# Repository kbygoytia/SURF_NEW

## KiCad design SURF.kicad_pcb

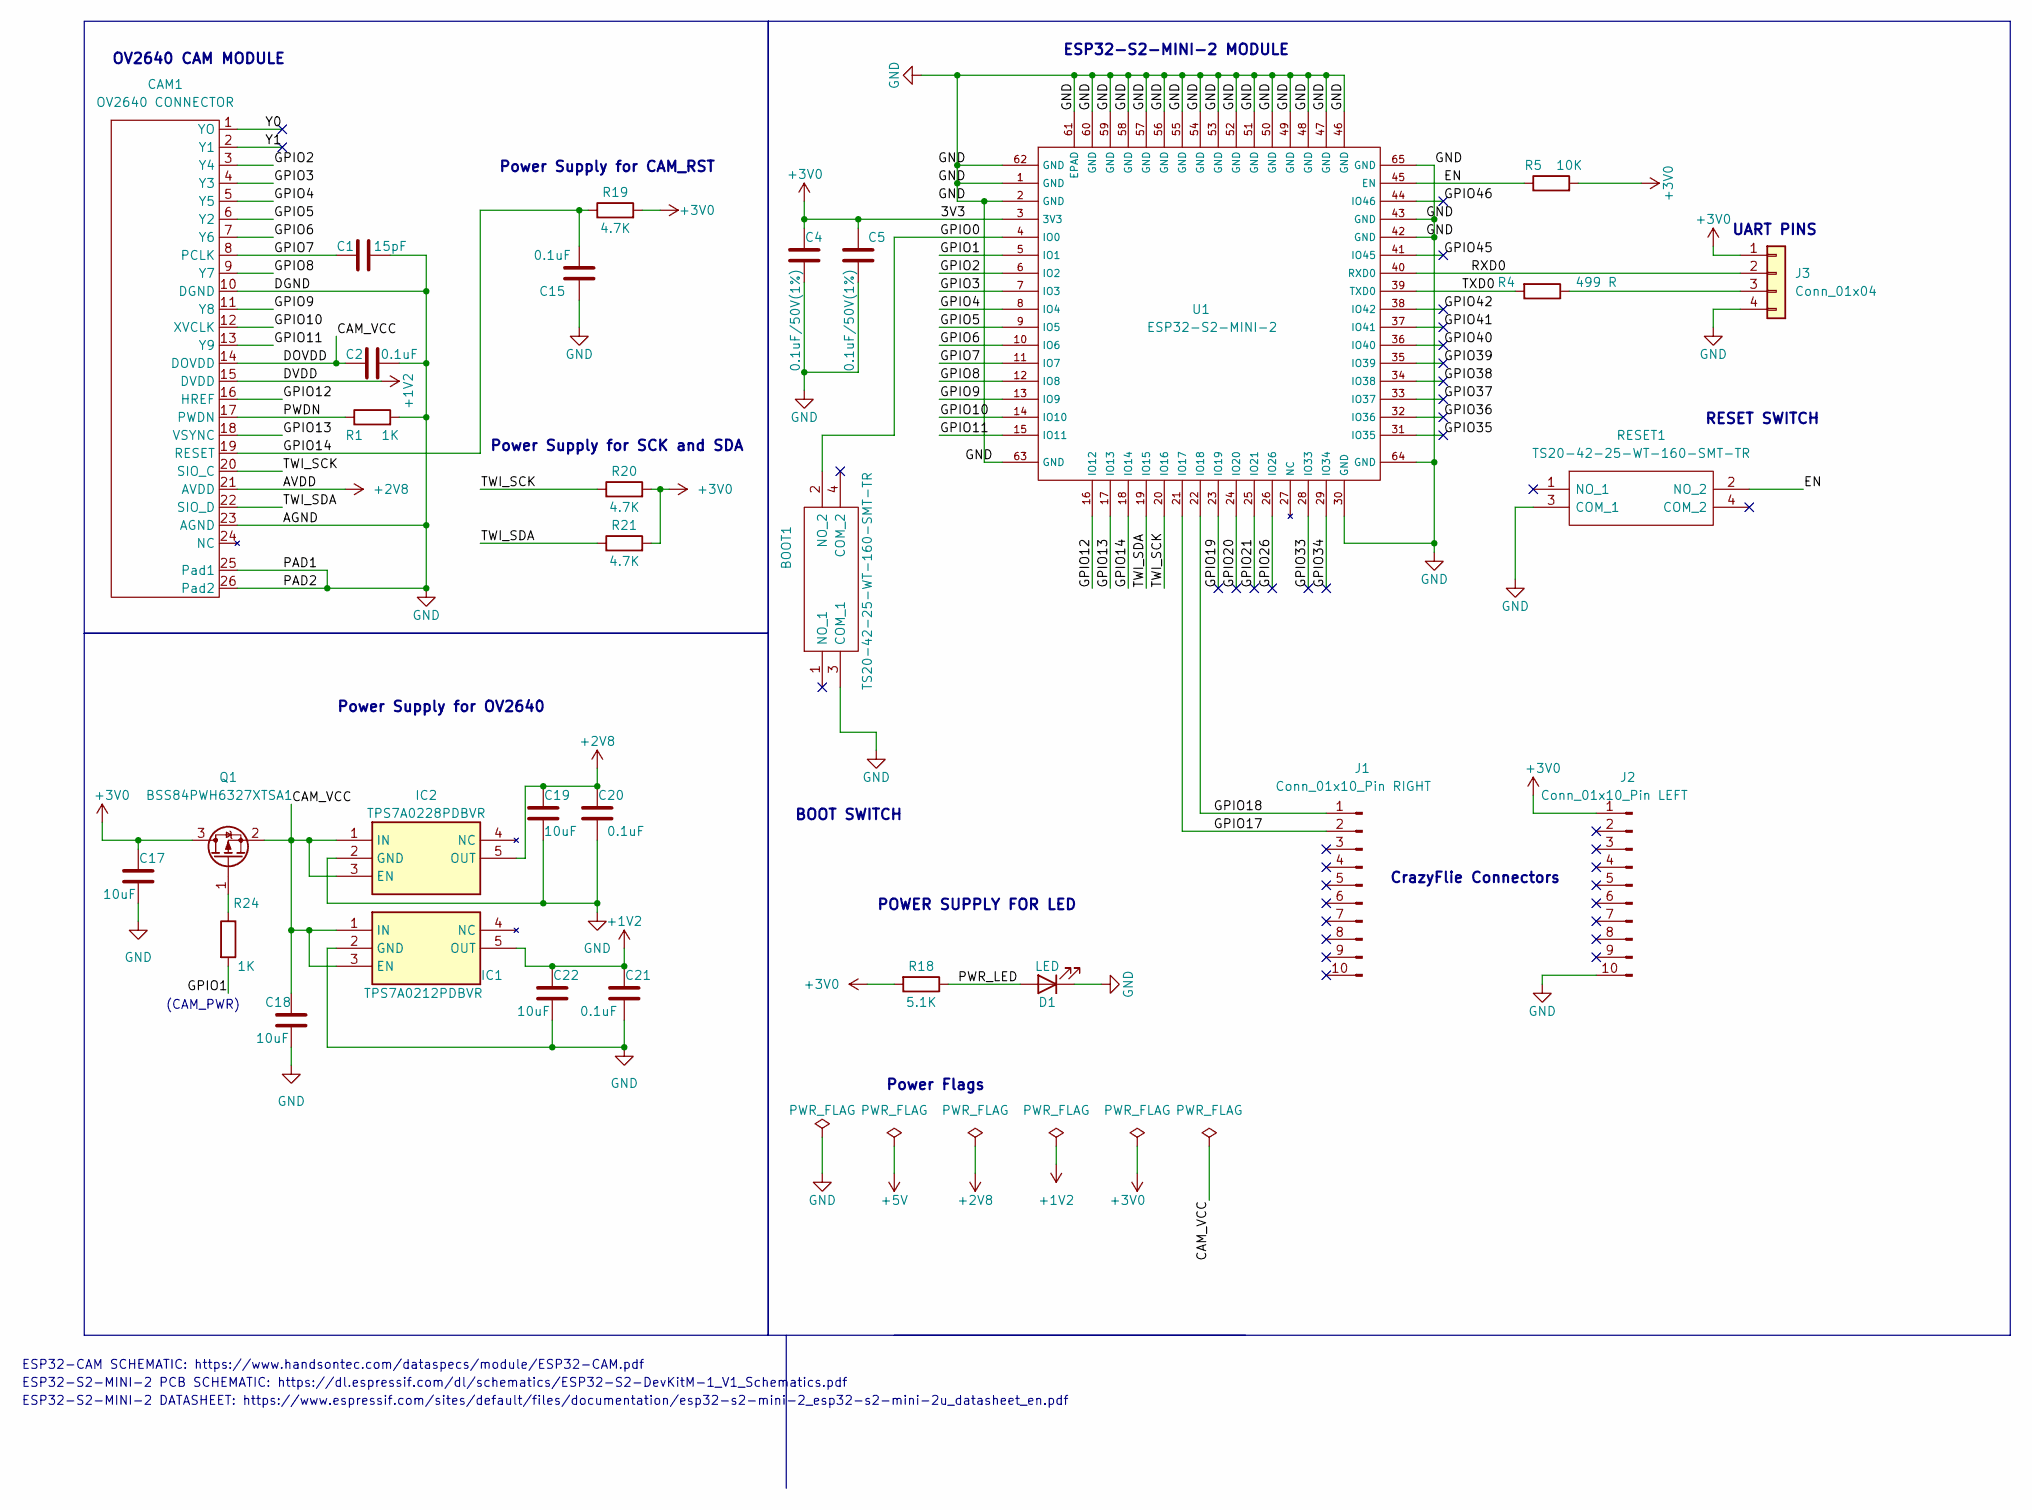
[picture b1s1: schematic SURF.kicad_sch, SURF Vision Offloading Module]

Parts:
BOOT1: TS20-42-25-WT-160-SMT-TR; TS204225WT160SMTTR; Mouser Part Number 179-TS204225WT160SMT
C1: 15pF; CAPC1608X87N
C2, C15, C20, C21: 0.1uF; CAPC1608X90N
C4, C5: 0.1uF/50V(1%); CAPC3216X170N
C17, C18, C19, C22: 10uF; CAPC2012X145N
CAM1: OV2640 CONNECTOR; ov2640-fcp_1
D1: LED; LED_0603_1608Metric
IC1: TPS7A0212PDBVR; SOT95P280X145-5N; Mouser Part Number 595-TPS7A0212PDBVR
IC2: TPS7A0228PDBVR; SOT95P280X145-5N; Mouser Part Number 595-TPS7A0228PDBVR
J1: Conn_01x10_Pin RIGHT; CONN_PINHEADERS_01X10_CRAZYFLIE
J2: Conn_01x10_Pin LEFT; CONN_PINHEADERS_01X10_CRAZYFLIE
J3: Conn_01x04; PinHeader_1x04_P2.54mm_Vertical
Q1: BSS84PWH6327XTSA1; SOT-523
R1, R24: 1K; R_0402_1005Metric
R4: 499 R; R_0402_1005Metric
R5: 10K; R_0402_1005Metric
R18: 5.1K; R_0402_1005Metric
R19, R20, R21: 4.7K; R_0402_1005Metric
RESET1: TS20-42-25-WT-160-SMT-TR; TS204225WT160SMTTR; Mouser Part Number 179-TS204225WT160SMT
U1: ESP32-S2-MINI-2

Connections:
+1V2: C21.1, C22.1, CAM1.15 (DVDD), IC1.5 (OUT)
+2V8: C19.1, C20.1, CAM1.21 (AVDD), IC2.5 (OUT)
+3V0: C4.1, C5.1, C17.1, J2.1, J3.1, Q1.3 (D), R5.2, R18.2, R19.2, R20.2, R21.2, U1.3 (3V3)
/CAM_VCC: C2.1, C18.1, CAM1.14 (DOVDD), IC1.1 (IN), IC1.3 (EN), IC2.1 (IN), IC2.3 (EN), Q1.2 (S)
/EN: R5.1, RESET1.2 (NO_2), U1.45 (EN)
/GPIO0: BOOT1.2 (NO_2), U1.4 (IO0)
/GPIO1: R24.2, U1.5 (IO1)
/GPIO2: CAM1.3 (Y4), U1.6 (IO2)
/GPIO3: CAM1.4 (Y3), U1.7 (IO3)
/GPIO4: CAM1.5 (Y5), U1.8 (IO4)
/GPIO5: CAM1.6 (Y2), U1.9 (IO5)
/GPIO6: CAM1.7 (Y6), U1.10 (IO6)
/GPIO7: C1.1, CAM1.8 (PCLK), U1.11 (IO7)
/GPIO8: CAM1.9 (Y7), U1.12 (IO8)
/GPIO9: CAM1.11 (Y8), U1.13 (IO9)
/GPIO10: CAM1.12 (XVCLK), U1.14 (IO10)
/GPIO11: CAM1.13 (Y9), U1.15 (IO11)
/GPIO12: CAM1.16 (HREF), U1.16 (IO12)
/GPIO13: CAM1.18 (VSYNC), U1.17 (IO13)
/GPIO14: C15.2, CAM1.19 (RESET), R19.1, U1.18 (IO14)
/GPIO17: J1.2, U1.21 (IO17)
/GPIO18: J1.1, U1.22 (IO18)
/GPIO19: U1.23 (IO19)
/GPIO20: U1.24 (IO20)
/GPIO21: U1.25 (IO21)
/GPIO26: U1.26 (IO26)
/GPIO33: U1.28 (IO33)
/GPIO34: U1.29 (IO34)
/GPIO35: U1.31 (IO35)
/GPIO36: U1.32 (IO36)
/GPIO37: U1.33 (IO37)
/GPIO38: U1.34 (IO38)
/GPIO39: U1.35 (IO39)
/GPIO40: U1.36 (IO40)
/GPIO41: U1.37 (IO41)
/GPIO42: U1.38 (IO42)
/GPIO45: U1.41 (IO45)
/GPIO46: U1.44 (IO46)
/PWDN: CAM1.17 (PWDN), R1.1
/PWR_LED: D1.2 (A), R18.1
/RXD0: J3.2, U1.40 (RXD0)
/TWI_SCK: CAM1.20 (SIO_C), R20.1, U1.20 (IO16)
/TWI_SDA: CAM1.22 (SIO_D), R21.1, U1.19 (IO15)
/TXD0: R4.2, U1.39 (TXD0)
/Y0: CAM1.1 (YO)
/Y1: CAM1.2 (Y1)
GND: BOOT1.3 (COM_1), C1.2, C2.2, C4.2, C5.2, C15.1, C17.2, C18.2, C19.2, C20.2, C21.2, C22.2, CAM1.10 (DGND), CAM1.23 (AGND), CAM1.25 (Pad1), CAM1.26 (Pad2), D1.1 (K), IC1.2 (GND), IC2.2 (GND), J2.10, J3.4, R1.2, RESET1.3 (COM_1), U1.1 (GND), U1.2 (GND), U1.30 (GND), U1.42 (GND), U1.43 (GND), U1.46 (GND), U1.47 (GND), U1.48 (GND), U1.49 (GND), U1.50 (GND), U1.51 (GND), U1.52 (GND), U1.53 (GND), U1.54 (GND), U1.55 (GND), U1.56 (GND), U1.57 (GND), U1.58 (GND), U1.59 (GND), U1.60 (GND), U1.61 (EPAD), U1.62 (GND), U1.63 (GND), U1.64 (GND), U1.65 (GND)
unnamed: J3.3, R4.1
unnamed: Q1.1 (G), R24.1

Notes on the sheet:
ESP32-S2-MINI-2 PCB SCHEMATIC: https://dl.espressif.com/dl/schematics/ESP32-S2-DevKitM-1_V1_Schematics.pdf
ESP32-S2-MINI-2 MODULE
ESP32-S2-MINI-2 DATASHEET: https://www.espressif.com/sites/default/files/documentation/esp32-s2-mini-2_esp32-s2-mini-2u_datasheet_en.pdf
UART PINS
POWER SUPPLY FOR LED
Power Supply for SCK and SDA
(CAM_PWR)
CrazyFlie Connectors
ESP32-CAM SCHEMATIC: https://www.handsontec.com/dataspecs/module/ESP32-CAM.pdf
RESET SWITCH
OV2640 CAM MODULE
Power Supply for CAM_RST
Power Flags
BOOT SWITCH
Power Supply for OV2640

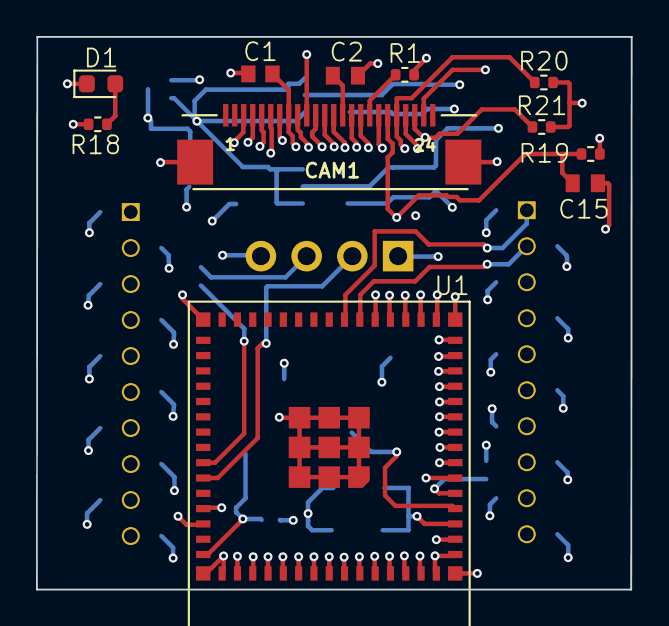
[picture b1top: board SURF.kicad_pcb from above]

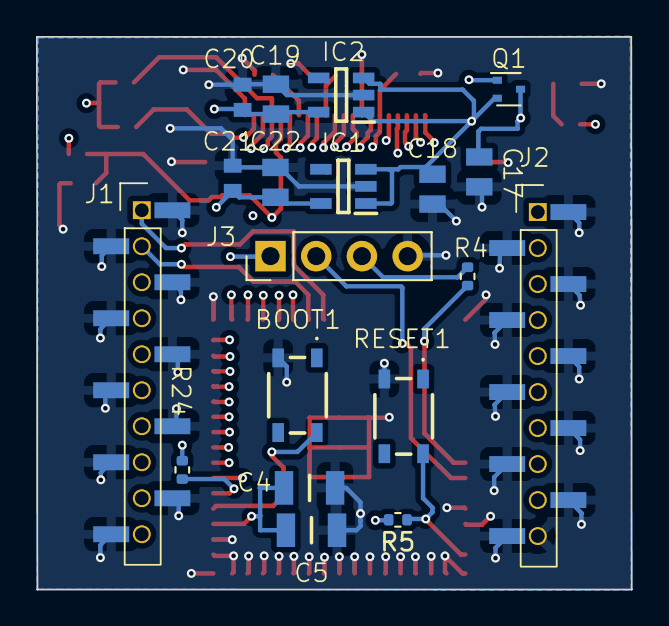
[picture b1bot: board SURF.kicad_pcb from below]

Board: 4 copper layers, 33.0 x 30.7 mm, 30 parts (19 on the bottom side), 31 nets.

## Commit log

2023-06-29 add file
2023-06-29 add readme
2023-07-07 new update
